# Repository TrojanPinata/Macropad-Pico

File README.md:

# Macropad-Pico

This is a 12-key macropad based off of the Raspberry Pi Pico with the intention of making something which is almost entirely 3d printable, cheap, and designed with the intention to show off the board, keycaps, and switches. Some key features of this board is the window for the microcontroller, center (separate) USB-C connector (with detachable cable), and a completely through-hole design.

This board is intended for people who want to be able to do the majority of the project on their own - only requiring you to send out the PCB to be made if you want to use one. A alternate switchplate is included for those wanting to handwire their boards.

I also made a [video if you want to make this yourself](https://youtu.be/6qyvscmvLPk).

## What you need

In order to actually make this you will need a few things (assuming you didn't get this as a kit and nothing is preassembled):

   - A soldering iron (+ flux, sponge, etc.)
   - A small phillips screwdriver
   - 4 ~12mm long M2 screws/bolts
   - A [USB-C female breakout board](https://a.co/d/hSMmR2M)
   - Some ~26 AWG wire
   - 12 1N4148 Diodes (or similar speed switching diodes)
   - 12 keyboard switches
   - 12 keycaps
   - A Pi Pico
   - The 3D printed case and switchplate
   - A USB-C cable
   - The provided firmware
   - The PCB (optional)
   - Male/Female 4-pin JST connectors (PH type) (optional, but recommended)

## Preparation 

(If you got this as a kit then this section can be mostly disregarded)

First thing is first, the case and switchplate will need to be printed. This size of this macropad is small enough to be printable on any 3D printer, so it should be pretty accessible. Be aware that tolerances and some shrink of the printed components is normal and should be accounted for. I printed mine with PLA, though most anything can be used. I made the switchplate at 100% infill and the case at 25% and they came out fine.

If you are using the PCB, then you can take the gerbers and send them off to JLCPCB or somewhere and get them made. The PCBs should cost ~$12 with shipping, don't overpay.

If you are doing this with a stock Pi Pico you might have clearance issues with the Micro USB port as it protrudes out a bit. This only occurs if you solder this flat, using headers this won't be an issue. It should fit with a slight bulge (0.1mm too high +/- 0.3mm) - this is mostly a remnant due to using a [Pico I designed myself](https://github.com/TrojanPinata/Pico) which does not have this issue. Shaving down the plate fixes this but it should not get in the way as long as the Pico is soldered down flat.

In this step I also recommend making the JST connectors. If you are using a PCB, cut down the pins on the female port before soldering them down, making sure they are flush on both sides so that the Pico will be flat when it is soldered down. This port will make the case and PCB easlily seperable when trying to do work on it. Making the JST connectors is kind of a mess, but watch a tutorial and be patient as to not mess them up. We will cover soldering the USB port to them in the next section.

## Building the board

At this point, you have everything in ready to be soldered, glued, and assembled. We will start by going over the soldering.

If you have never soldered anything before let me give you some tips to be successful:
   
   - Tin all wires before soldering. When soldering the wire to the thing, you shouldn't need that much as the wire already has some on the tip and will easily attach to the hole/pad.
   - Use flux. Liquid flux, flux pen, doesn't matter - this will make it way easier to make the solder stick.
   - Clean your iron tip with brass brush. This will get rid of the burn off which will make the solder not melt to the tip.
   - Don't let the iron get too hot, stay around 280C for lead-free solder. 
   - Use whatever tip you are comfortable with, the smaller the more percise, but somewhere a bit larger may be easier for beginners.

To start, if you haven't attached the female JST connector to the board (ignore if kit), put the connector on the board and mark how much extra wire pokes through the other side of the board, and cut the remainder. Then put some flux in the holes with the connector and solder, using just enough to fill the hole and not create a large bump.

Since we are working on that, then it is probably also necessary to solder the USB port now. The terminals are labeled on both the board and connector, so make sure to match them up. Use flux and tinned wire, and don't leave the iron on the pads too long - only enough to reflow the solder from the tinned wires to the breakout board.

With this, the connector is done and the Pico can be soldered down. To do this, the easiest way is to flatten the Pico in place on the board (if it doesn't want to stay then use tape temporarily) and solder the corners to their pads, then go back and get all of the pads in the middle. Use flux and use a amount of solder to connect the top of the pad with the PCB. On the bottom of the board, there is a cutout for accessing the TP2 and TP3 pads. I recommend soldering two short lengths of wire to them before putting the Pico down, as it makes access to them slightly easier, but it can be done after. Connect those wires to the DP and DN holes to the left on the backside of the PCB. 

After doing that, you can drop the diodes in, verifying that they are in the proper orientation. Bend the legs out a bit, and flip the board over. They should stay in, but also the surface below should keep pressure on them so they are flat on the front side. Flux, solder, then clip the legs off (protect your eyes!). 

At this point, you are almost done. You now need to pop your switches into the switchplate, and try to fanagle the switches in the array into the holes on the PCB. This is tricky, but be patient. Once they are all in, solder the pins in. The PCB and switchplate should now be sort of connected via the switches.

At this time, you should glue the USB-C connector into the case and connect it to the PCB. Then, the PCB-switchplate combo should be dropped into the case and screwed in. With that, you are ready to flash the firmware and put on the keycaps.

## Firmware

I will not go over building your own firmware here, as that is far outside the scope of this guide. The firmware provided can be flashed to the pico but plugging in the PCB or Pico to a computer while holding the `BOOTSEL` button and dragging the provided `.uf2` file onto the drive that `RPI-RP2` drive that appears. This will flash the board and you will be ready to go. (Test it with a [keyboard tester](https://key-test.com/) to make sure it works with the hardware)

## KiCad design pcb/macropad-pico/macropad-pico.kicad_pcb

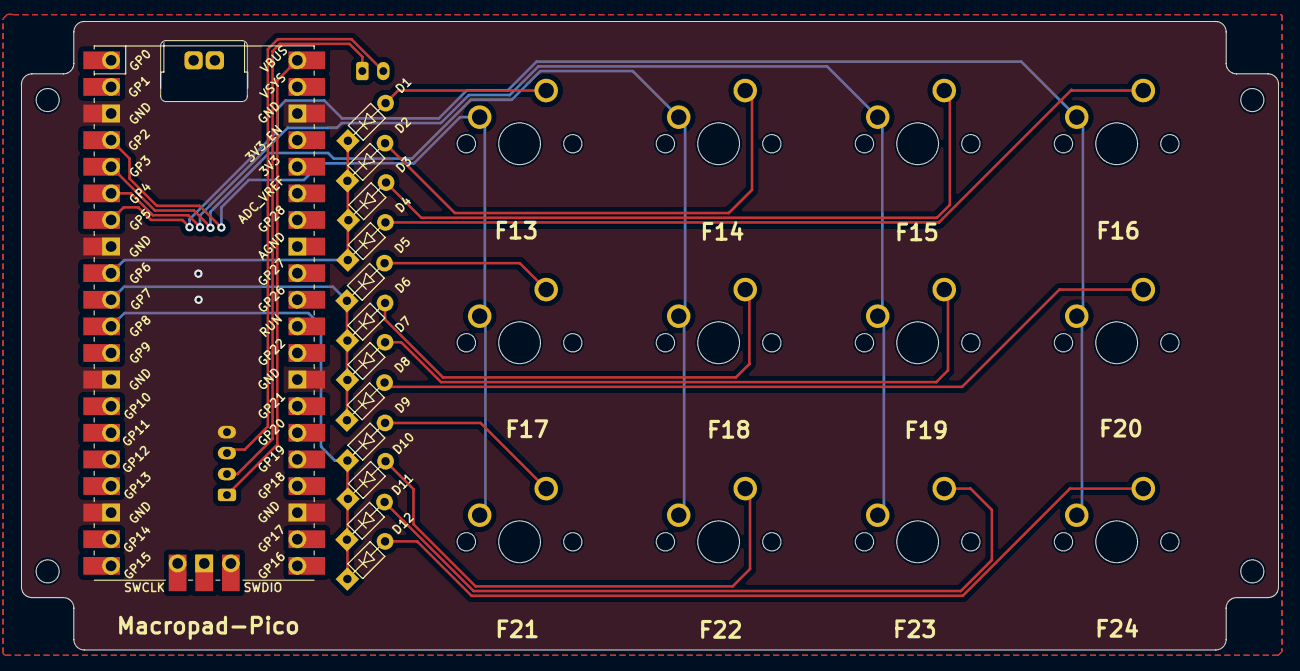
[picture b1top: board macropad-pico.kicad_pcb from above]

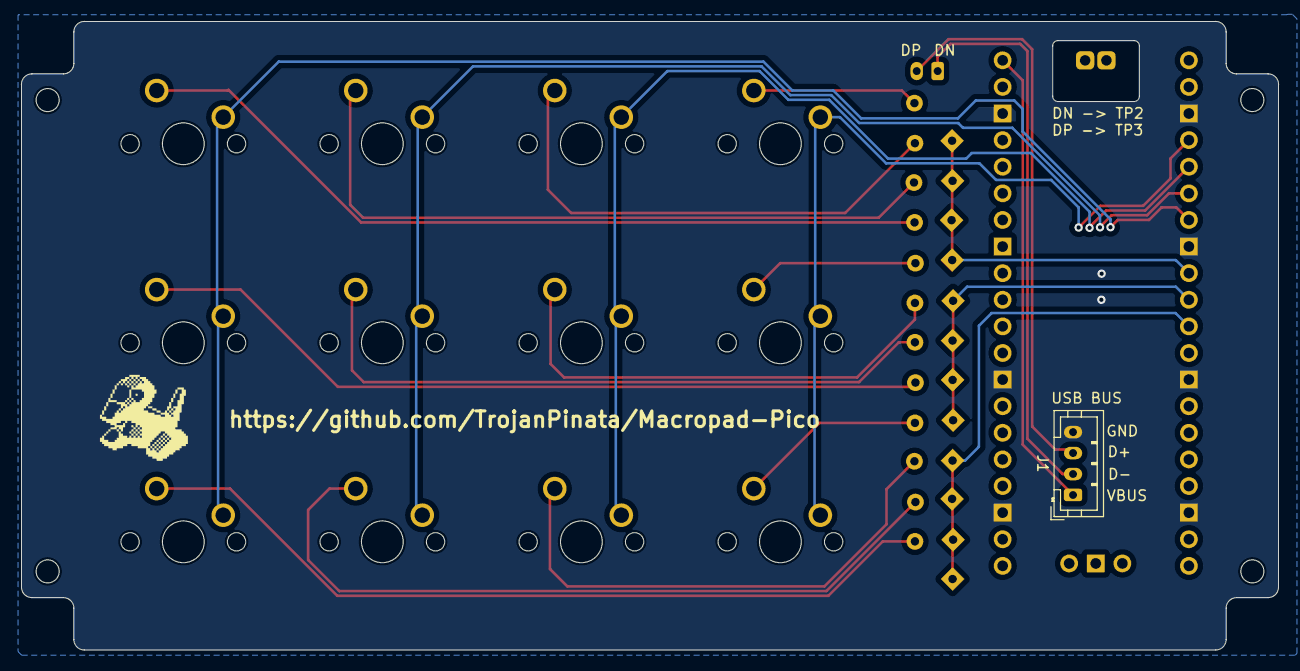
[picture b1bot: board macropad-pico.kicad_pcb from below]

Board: 2 copper layers, 120.0 x 60.0 mm, 27 parts (2 on the bottom side), 23 nets.

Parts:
D1, D2, D3, D4, D5, D6, D7, D8, D9, D10, D11, D12: D; D_DO-35_SOD27_P5.08mm_Horizontal
J1: Conn_01x04_Socket; JST_PH_B4B-PH-K_1x04_P2.00mm_Vertical
J2: Conn_01x02_Socket; JST_PH_B2B-PH-K_1x02_P2.00mm_Vertical
RPI1: Pico; RPi_Pico_SMD_TH
SW-1U-1, SW-1U-2, SW-1U-3, SW-1U-4, SW-1U-5, SW-1U-6, SW-1U-7, SW-1U-8, SW-1U-9, SW-1U-10, SW-1U-11, SW-1U-12: KEYSW; MXOnly-1U-NoLED

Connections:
/DN: J1.2, J2.1
/DP: J1.3, J2.2
/col0: RPI1.4 (GPIO2), SW-1U-1.1, SW-1U-5.1, SW-1U-9.1
/col1: RPI1.5 (GPIO3), SW-1U-2.1, SW-1U-6.1, SW-1U-10.1
/col2: RPI1.6 (GPIO4), SW-1U-3.1, SW-1U-7.1, SW-1U-11.1
/col3: RPI1.7 (GPIO5), SW-1U-4.1, SW-1U-8.1, SW-1U-12.1
/row0: D1.1, D2.1, D3.1, D4.1, RPI1.9 (GPIO6)
/row1: D5.1, D6.1, D7.1, D8.1, RPI1.10 (GPIO7)
/row2: D9.1, D10.1, D11.1, D12.1, RPI1.11 (GPIO8)
GND: J1.4, RPI1.3 (GND), RPI1.8 (GND), RPI1.13 (GND), RPI1.18 (GND), RPI1.23 (GND), RPI1.28 (GND), RPI1.38 (GND)
unnamed: D1.2, SW-1U-1.2
unnamed: D2.2, SW-1U-2.2
unnamed: D3.2, SW-1U-3.2
unnamed: D4.2, SW-1U-4.2
unnamed: D5.2, SW-1U-5.2
unnamed: D6.2, SW-1U-6.2
unnamed: D7.2, SW-1U-7.2
unnamed: D8.2, SW-1U-8.2
unnamed: D9.2, SW-1U-9.2
unnamed: D10.2, SW-1U-10.2
unnamed: D11.2, SW-1U-11.2
unnamed: D12.2, SW-1U-12.2
VCC: J1.1, RPI1.40 (VBUS)

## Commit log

2024-08-20 project init
2024-08-20 firmware built and Readme written
2024-09-04 Added images
2024-09-04 added images to readme
2024-09-05 added video link
2024-09-26 quick note
